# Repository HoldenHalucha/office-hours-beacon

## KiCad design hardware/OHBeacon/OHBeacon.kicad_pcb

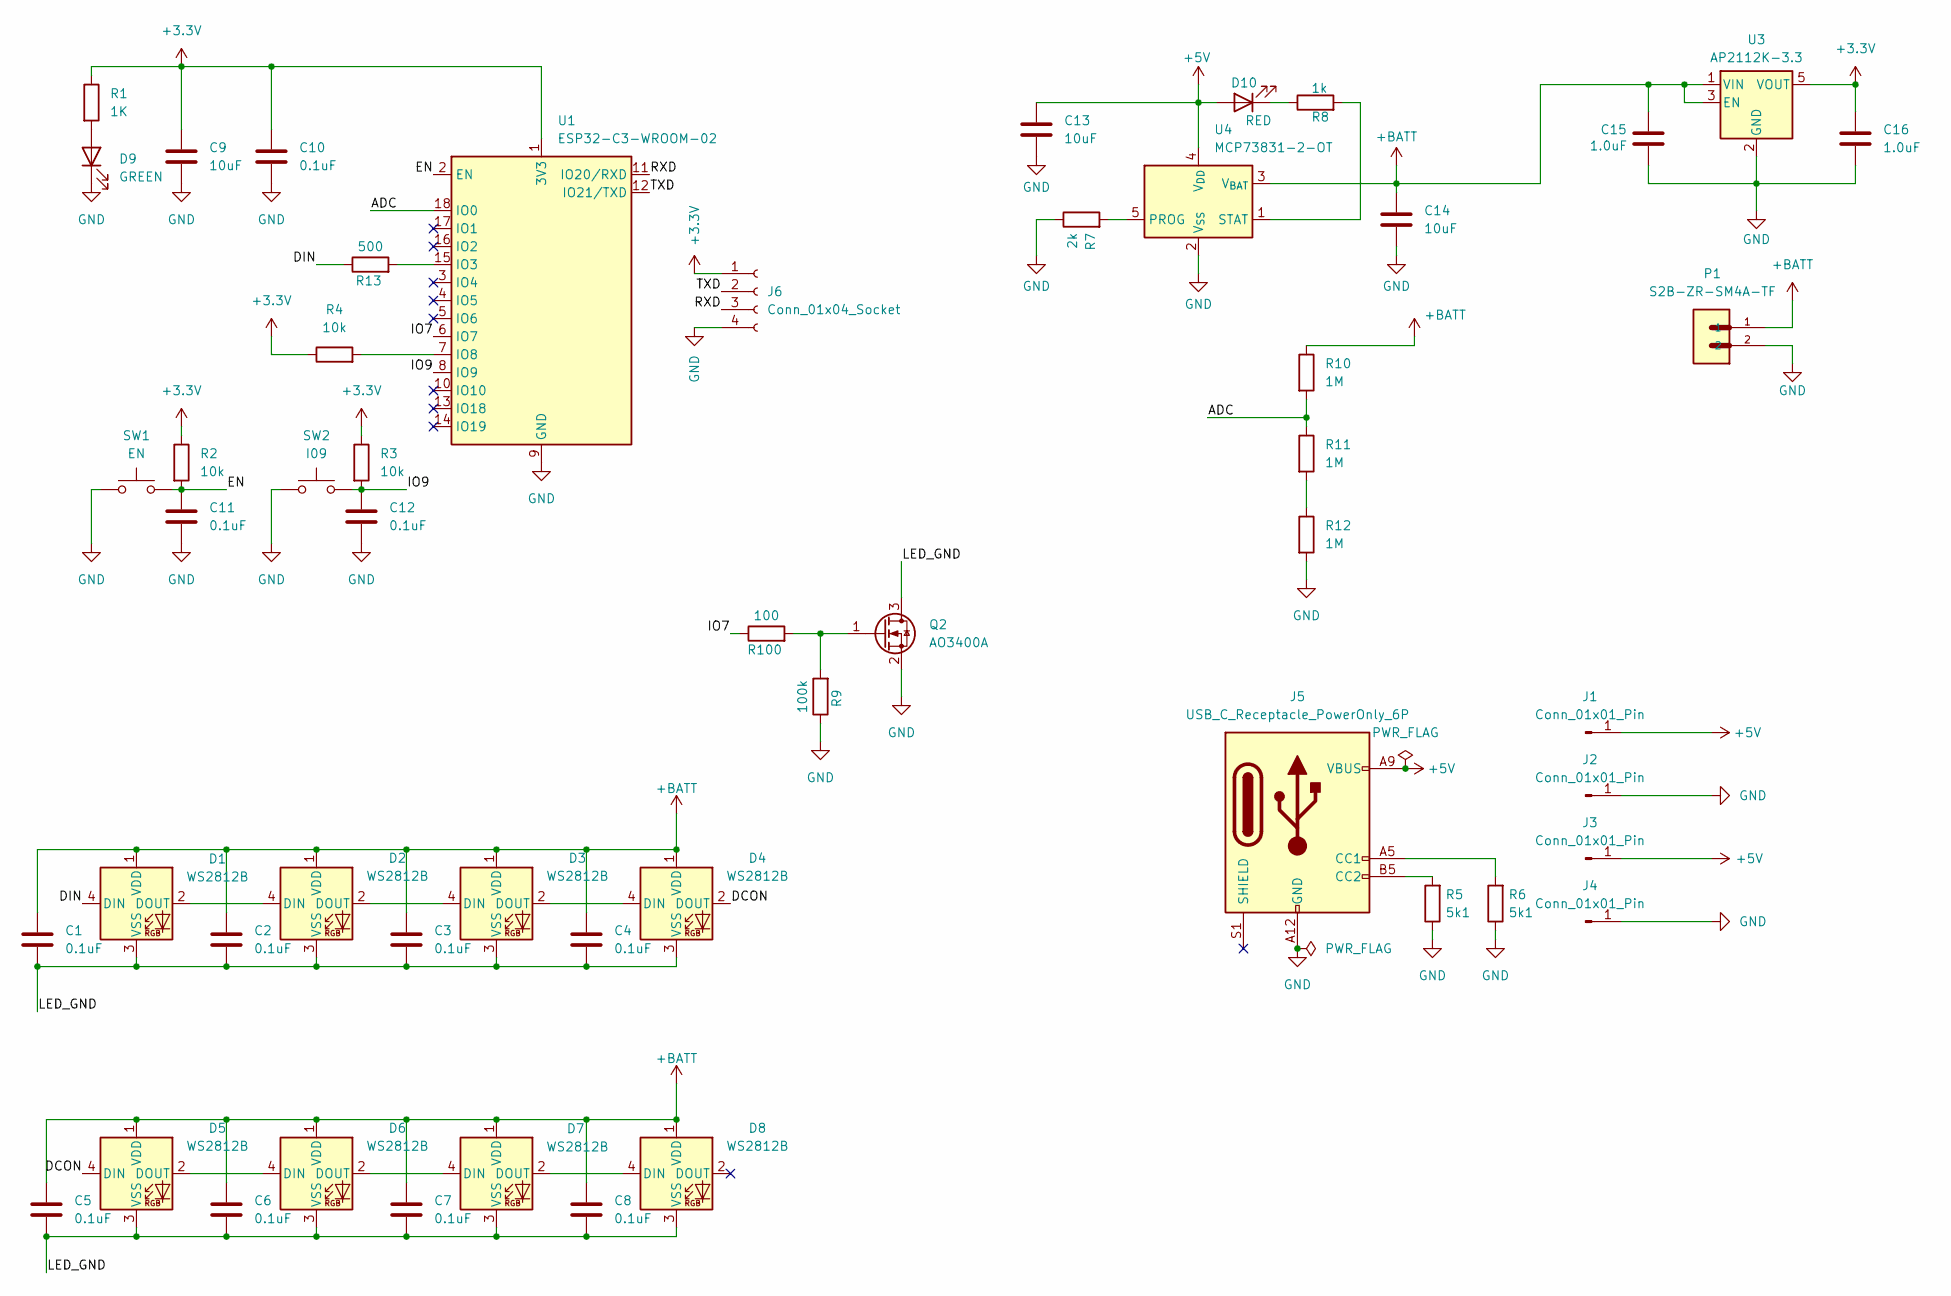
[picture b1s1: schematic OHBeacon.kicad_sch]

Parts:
C1, C2, C3, C4, C5, C6, C7, C8, C10, C11, C12: 0.1uF; C_0805_2012Metric_Pad1.18x1.45mm_HandSolder
C9, C13, C14: 10uF; C_0805_2012Metric_Pad1.18x1.45mm_HandSolder
C15, C16: 1.0uF; C_0805_2012Metric_Pad1.18x1.45mm_HandSolder
D1, D2, D3, D4, D5, D6, D7, D8: WS2812B; LED_WS2812B_PLCC4_5.0x5.0mm_P3.2mm
D9: GREEN; LED_0805_2012Metric_Pad1.15x1.40mm_HandSolder
D10: RED; LED_0805_2012Metric_Pad1.15x1.40mm_HandSolder
J1, J2, J3, J4: Conn_01x01_Pin; SolderWire-1sqmm_1x01_D1.4mm_OD3.9mm
J5: USB_C_Receptacle_PowerOnly_6P; USB_C_Receptacle_GCT_USB4135-GF-A_6P_TopMnt_Horizontal
J6: Conn_01x04_Socket; PinHeader_1x04_P2.54mm_Vertical
P1: S2B-ZR-SM4A-TF; JST_S2B-ZR-SM4A-TF
Q2: AO3400A; SOT-23
R1: 1K; R_0805_2012Metric_Pad1.20x1.40mm_HandSolder
R2, R3, R4: 10k; R_0805_2012Metric_Pad1.20x1.40mm_HandSolder
R5, R6: 5k1; R_0805_2012Metric_Pad1.20x1.40mm_HandSolder
R7: 2k; R_0805_2012Metric_Pad1.20x1.40mm_HandSolder
R8: 1k; R_0805_2012Metric_Pad1.20x1.40mm_HandSolder
R9: 100k; R_0805_2012Metric_Pad1.20x1.40mm_HandSolder
R10, R11, R12: 1M; R_0805_2012Metric_Pad1.20x1.40mm_HandSolder
R13: 500; R_0805_2012Metric_Pad1.20x1.40mm_HandSolder
R100: 100; R_0805_2012Metric_Pad1.20x1.40mm_HandSolder
SW1: EN; SW_PUSH_6mm
SW2: I09; SW_PUSH_6mm
U1: ESP32-C3-WROOM-02
U3: AP2112K-3.3; SOT-23-5
U4: MCP73831-2-OT; SOT-23-5

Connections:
+3.3V: C9.1, C10.1, C16.1, J6.1, R1.1, R2.1, R3.1, R4.1, U1.1 (3V3), U3.5 (VOUT)
+5V: C13.1, D10.2 (A), J1.1, J3.1, J5.A9 (VBUS), J5.B9 (VBUS), U4.4 (V_{DD})
+BATT: C1.1, C2.1, C3.1, C4.1, C5.1, C6.1, C7.1, C8.1, C14.1, C15.1, D1.1 (VDD), D2.1 (VDD), D3.1 (VDD), D4.1 (VDD), D5.1 (VDD), D6.1 (VDD), D7.1 (VDD), D8.1 (VDD), P1.1, R10.1, U3.1 (VIN), U3.3 (EN), U4.3 (V_{BAT})
/ADC: R10.2, R11.1, U1.18 (IO0)
/DCON: D4.2 (DOUT), D5.4 (DIN)
/DIN: D1.4 (DIN), R13.1
/EN: C11.1, R2.2, SW1.2, U1.2 (EN)
/IO7: R100.1, U1.6 (IO7)
/IO9: C12.1, R3.2, SW2.2, U1.8 (IO9)
/LED_GND: C1.2, C2.2, C3.2, C4.2, C5.2, C6.2, C7.2, C8.2, D1.3 (VSS), D2.3 (VSS), D3.3 (VSS), D4.3 (VSS), D5.3 (VSS), D6.3 (VSS), D7.3 (VSS), D8.3 (VSS), Q2.3 (D)
/RXD: J6.3, U1.11 (IO20/RXD)
/TXD: J6.2, U1.12 (IO21/TXD)
GND: C9.2, C10.2, C11.2, C12.2, C13.2, C14.2, C15.2, C16.2, D9.1 (K), J2.1, J4.1, J5.A12 (GND), J5.B12 (GND), J6.4, P1.2, Q2.2 (S), R5.1, R6.1, R7.1, R9.1, R12.2, SW1.1, SW2.1, U1.9 (GND), U1.19 (GND), U3.2 (GND), U4.2 (V_{SS})
unnamed: D1.2 (DOUT), D2.4 (DIN)
unnamed: D2.2 (DOUT), D3.4 (DIN)
unnamed: D3.2 (DOUT), D4.4 (DIN)
unnamed: D5.2 (DOUT), D6.4 (DIN)
unnamed: D6.2 (DOUT), D7.4 (DIN)
unnamed: D7.2 (DOUT), D8.4 (DIN)
unnamed: D9.2 (A), R1.2
unnamed: D10.1 (K), R8.1
unnamed: J5.A5 (CC1), R6.2
unnamed: J5.B5 (CC2), R5.2
unnamed: Q2.1 (G), R9.2, R100.2
unnamed: R11.2, R12.1
unnamed: R13.2, U1.15 (IO3)
unnamed: R4.2, U1.7 (IO8)
unnamed: R7.2, U4.5 (PROG)
unnamed: R8.2, U4.1 (STAT)

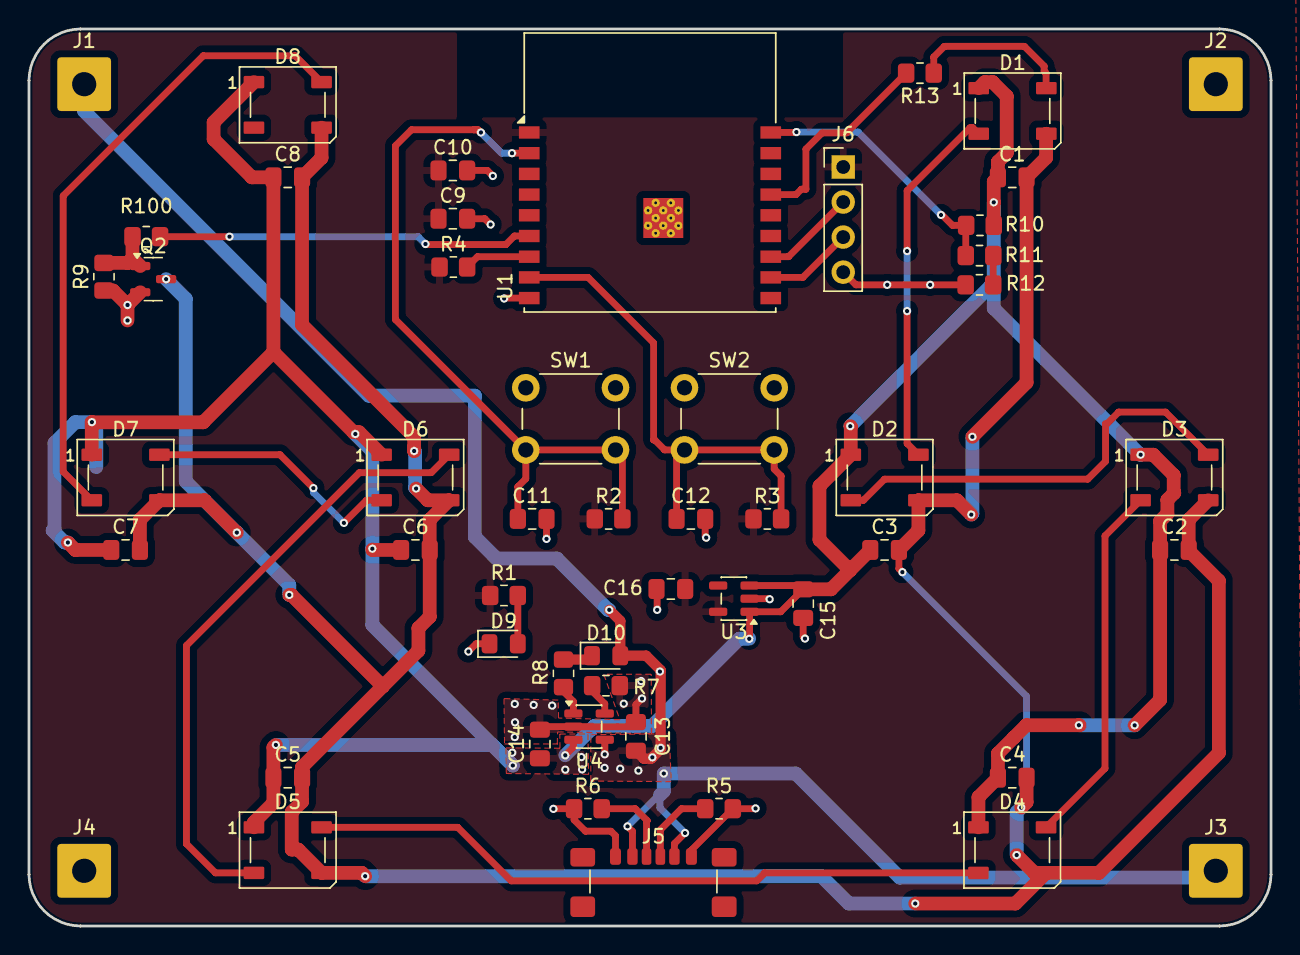
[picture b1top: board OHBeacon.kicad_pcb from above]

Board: 2 copper layers, 90.0 x 65.0 mm, 53 parts (1 on the bottom side), 29 nets.

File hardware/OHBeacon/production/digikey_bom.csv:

Qty,Part Number,Reference,Description
330,KGM21NR71H104KT,C1 C10 C11 C12 C2 C3 C4 C5 C6 C7 C8,0.1uF capacitor 0805
90,CL21A106KOQNNNE,C13 C14 C9,10uF capacitor 0805
60,CL21B105KBFNNNE,C15 C16,1.0uF capacitor 0805
30,LS R976-NR-1-0-20-R18,D10,Red LED 0805
30,LG R971-KN-1-0-20-R18,D9,Green LED 0805
120,ED9009-ND,J1 J2 J3 J4,Wire Solder Pin 1x01
30,USB4135-GF-A,J5,USB-C Power-Only Receptacle
5,PRPC040SACN-RC,J6,1x04 Pin Header Vertical 2.54mm
30,S2B-ZR-SM4A-TF,P1,JST S2B-ZR-SM4A-TF connector
30,AO3400A,Q2,AO3400A MOSFET SOT-23
60,RR1220P-102-D,R1 R8,1K resistor 0805
90,RG2012P-105-B-T5,R10 R11 R12,1M resistor 0805
30,ERA-6AEB101V,R100,100 ohm resistor 0805
30,CRGCQ0805J470R,R13,500 ohm resistor 0805
90,CRCW080510K0FKEA,R2 R3 R4,10K resistor 0805
60,RC0805JR-075K1L,R5 R6,5.1K resistor 0805
30,ERA-6AEB202V,R7,2K resistor 0805
30,RC0805FR-07100KL,R9,100K resistor 0805
30,Y97HT21A1EAFP,SW1,Pushbutton 6mm
30,Y97HT21A1EAFP,SW2,Pushbutton 6mm
30,ESP32-C3-WROOM-02-N4,U1,ESP32-C3-WROOM-02 module
30,AP2112K-3.3TRG1,U3,3.3V LDO regulator SOT-23-5

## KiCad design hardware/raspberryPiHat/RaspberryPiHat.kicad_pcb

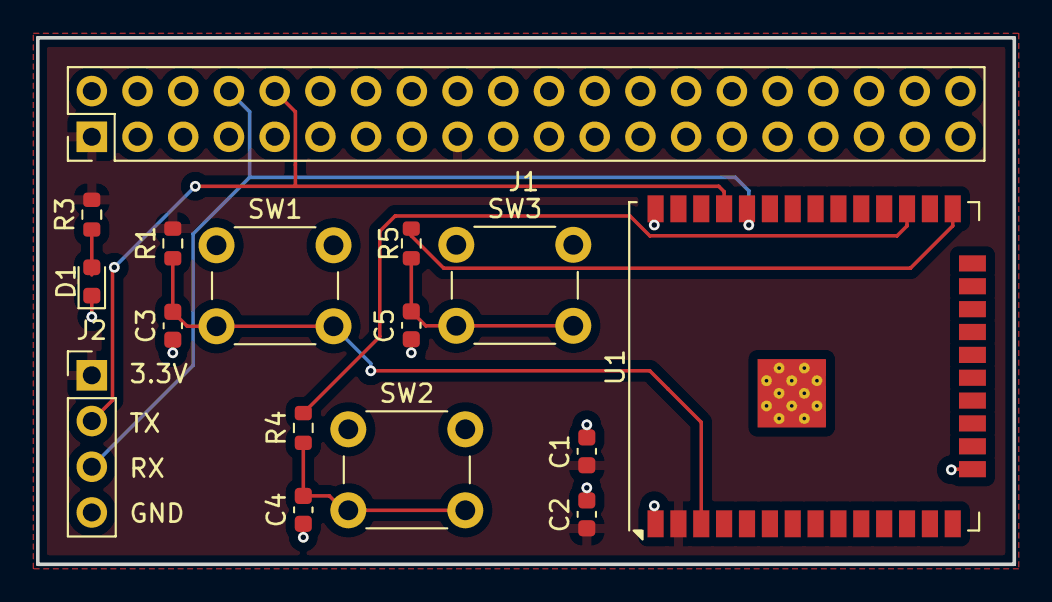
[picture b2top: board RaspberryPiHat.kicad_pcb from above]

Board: 2 copper layers, 54.2 x 29.2 mm, 16 parts (0 on the bottom side), 10 nets.

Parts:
C1: 22uF; C_0603_1608Metric
C2, C3, C4, C5: 0.1uF; C_0603_1608Metric
D1: LED; LED_0603_1608Metric
J1: Raspberry_Pi_2_3; PinHeader_2x20_P2.54mm_Vertical
J2: Conn_01x04_Socket; PinHeader_1x04_P2.54mm_Vertical
R1, R4, R5: 10k; R_0603_1608Metric
R3: 150; R_0603_1608Metric
SW1, SW2, SW3: SW_Push; SW_PUSH_6mm
U1: ESP32-WROOM-32U

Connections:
+3.3V: C1.1, C2.1, J1.1 (3V3), J1.17 (3V3), J2.1, R1.1, R3.1, U1.2 (VDD)
/IO0: R5.1, U1.25 (IO0)
/MODE: R4.1, U1.27 (IO16)
/RXD0: J1.8 (GPIO14/TXD), J2.3, U1.34 (RXD0/IO3)
/TXD0: J1.10 (GPIO15/RXD), J2.2, U1.35 (TXD0/IO1)
GND: C1.2, C2.2, C3.2, C4.2, C5.2, D1.1 (K), J1.6 (GND), J1.9 (GND), J1.14 (GND), J1.20 (GND), J1.25 (GND), J1.30 (GND), J1.34 (GND), J1.39 (GND), J2.4, SW1.1, SW2.1, SW3.1, U1.1 (GND), U1.15 (GND), U1.38 (GND), U1.39 (GND)
unnamed: C4.1, R4.2, SW2.2
unnamed: C5.1, R5.2, SW3.2
unnamed: D1.2 (A), R3.2
unnamed: C3.1, R1.2, SW1.2, U1.3 (EN)

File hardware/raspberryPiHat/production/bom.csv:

Designator,Footprint,Quantity,Value,LCSC Part #
C1,0603,1,22uF,
"C2, C3, C4, C5",0603,4,0.1uF,
D1,0603,1,LED,
J1,PinHeader_2x20_P2.54mm_Vertical,1,Raspberry_Pi_2_3,
J2,PinHeader_1x04_P2.54mm_Vertical,1,Conn_01x04_Socket,
"R1, R4, R5",0603,3,10k,
R3,0603,1,150,
"SW1, SW2, SW3",SW_PUSH_6mm,3,SW_Push,C455109
U1,ESP32-WROOM-32U,1,ESP32-WROOM-32U,C328062

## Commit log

2025-09-24 first commit!
2025-09-25 Added anither fetch function
    The added fetch_and_print_json() function continuously fetch and print JSON to console.
2025-09-26 Parametrized OH queue fetch function for all courses
    Provide a course id as shown in OH queue to fetch from that specific course
2025-09-28 Added multithreading to monitor multiple courses
2025-10-02 raspberry pi hat pcb rev 1
2025-10-02 Code to test ESP-NOW communication strength, strong results observed
2025-10-03 Added serial module
2025-10-05 Modified serial interface and added cookie file
2025-10-11 first commit for OH student beacon
2025-10-11 oh student beacon pcb first commit
2025-10-16 Milestone 1 Code
2025-10-18 Added a test file for development purpose
    This test file will not be ran on raspi.
2025-10-18 Added active course search based on request location and base station ID
2025-10-22 Added "Fetch" class for better encapsulation; Added thread manager to Fetch class
2025-10-22 Added location validation per base station
2025-10-23 esp32c3 low power experimentation with ESP-IDF
2025-10-23 new sch
2025-10-25 Some small changes to receiver code for power saving experimentation.
2025-10-26 prelim beacon pcb
2025-10-26 Changed some stuff in the schematic :)
2025-10-26 Finished fetch manager and updated rasPI firmware with the new Fetcher class
2025-10-27 updated beacon
2025-10-27 updated rpi
2025-10-28 okay it's fine for prod ig
2025-10-28 production folders for both PCBs
2025-10-28 Added course color and reworked some course thread interface
2025-10-28 Updated serial interface
2025-11-03 intial changes
2025-11-03 updated transm. code
2025-11-03 more
2025-11-03 quick fix for testing
2025-11-04 fixed the mac address sending stuff
2025-11-04 Fetcher updated to work on eecsoh.eecs
2025-11-06 Reverted main to work with oh.eecs
    This commit makes main branch work with oh.eecs.
    Another branch, eecsoh, works with eecsoh.eecs.
2025-11-12 new oh beacon schematic and early routing
2025-11-12 new charging
2025-11-12 get james approval
2025-11-14 final pcb?
2025-11-14 for aryan
2025-11-14 even more final PCB???
2025-11-14 BOM and Fabrication stuff
2025-11-15 Update BOM with latest edits
2025-11-15 Add digikey BOM
2025-11-20 Update esp32_receiver.c
    changes to the receiver code with transmitter-receiver packet format
2025-11-20 simple_arduino_esp-now_to_blast_messages/sketch_oct24a.ino
    changes include arduino code for a transmitter to just spam receivers with test values. I have been using this for testing
2025-11-21 more changes
2025-11-24 more stuff
2025-11-24 added directory for currently partially complete Android app code
2025-11-24 fixed bug in fetcher and updated mac addrs
2025-11-24 fixed serial interface
2025-11-25 working transmitter + receiver code
2025-11-25 Added repeating serial interface. FIxed bug in fetcher.
2025-12-01 Added more queue status and instructor defined course color
2025-12-02 Added dynamic color update
    Course color can now be updated for active beacons
2025-12-02 mostly working beacon code. gonna change a lot but we could run this if we wanted
2025-12-02 repeats -3 message
2025-12-02 should be mostly working receiver code + power usage data
2025-12-03 Updated custom course color format
2025-12-04 Updated serial
2025-12-07 final code used at expo
2025-12-10 Cookies now last much longer
    Cookies now expires on Wednesday, July 9, 2279, 2:46:31 AM GMT-04:00 DST
2026-01-02 changed the fetcher files so that they don't use an absolute path. Changed the session cookies
